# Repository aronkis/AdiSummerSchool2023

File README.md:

# AnalogDevices Summer School 2023

This is a repository for the Analog Devices summer school 2023.
We made a accelerometer application from designing the schematics to writing the code for the application.
We used a ADXL327 as an accelerometer and an AD5592R as the ADC.
Using KiCad we designed the schematics for this project as well as the layout.
The linux drivers were written in C, and the applications in C and in Python.

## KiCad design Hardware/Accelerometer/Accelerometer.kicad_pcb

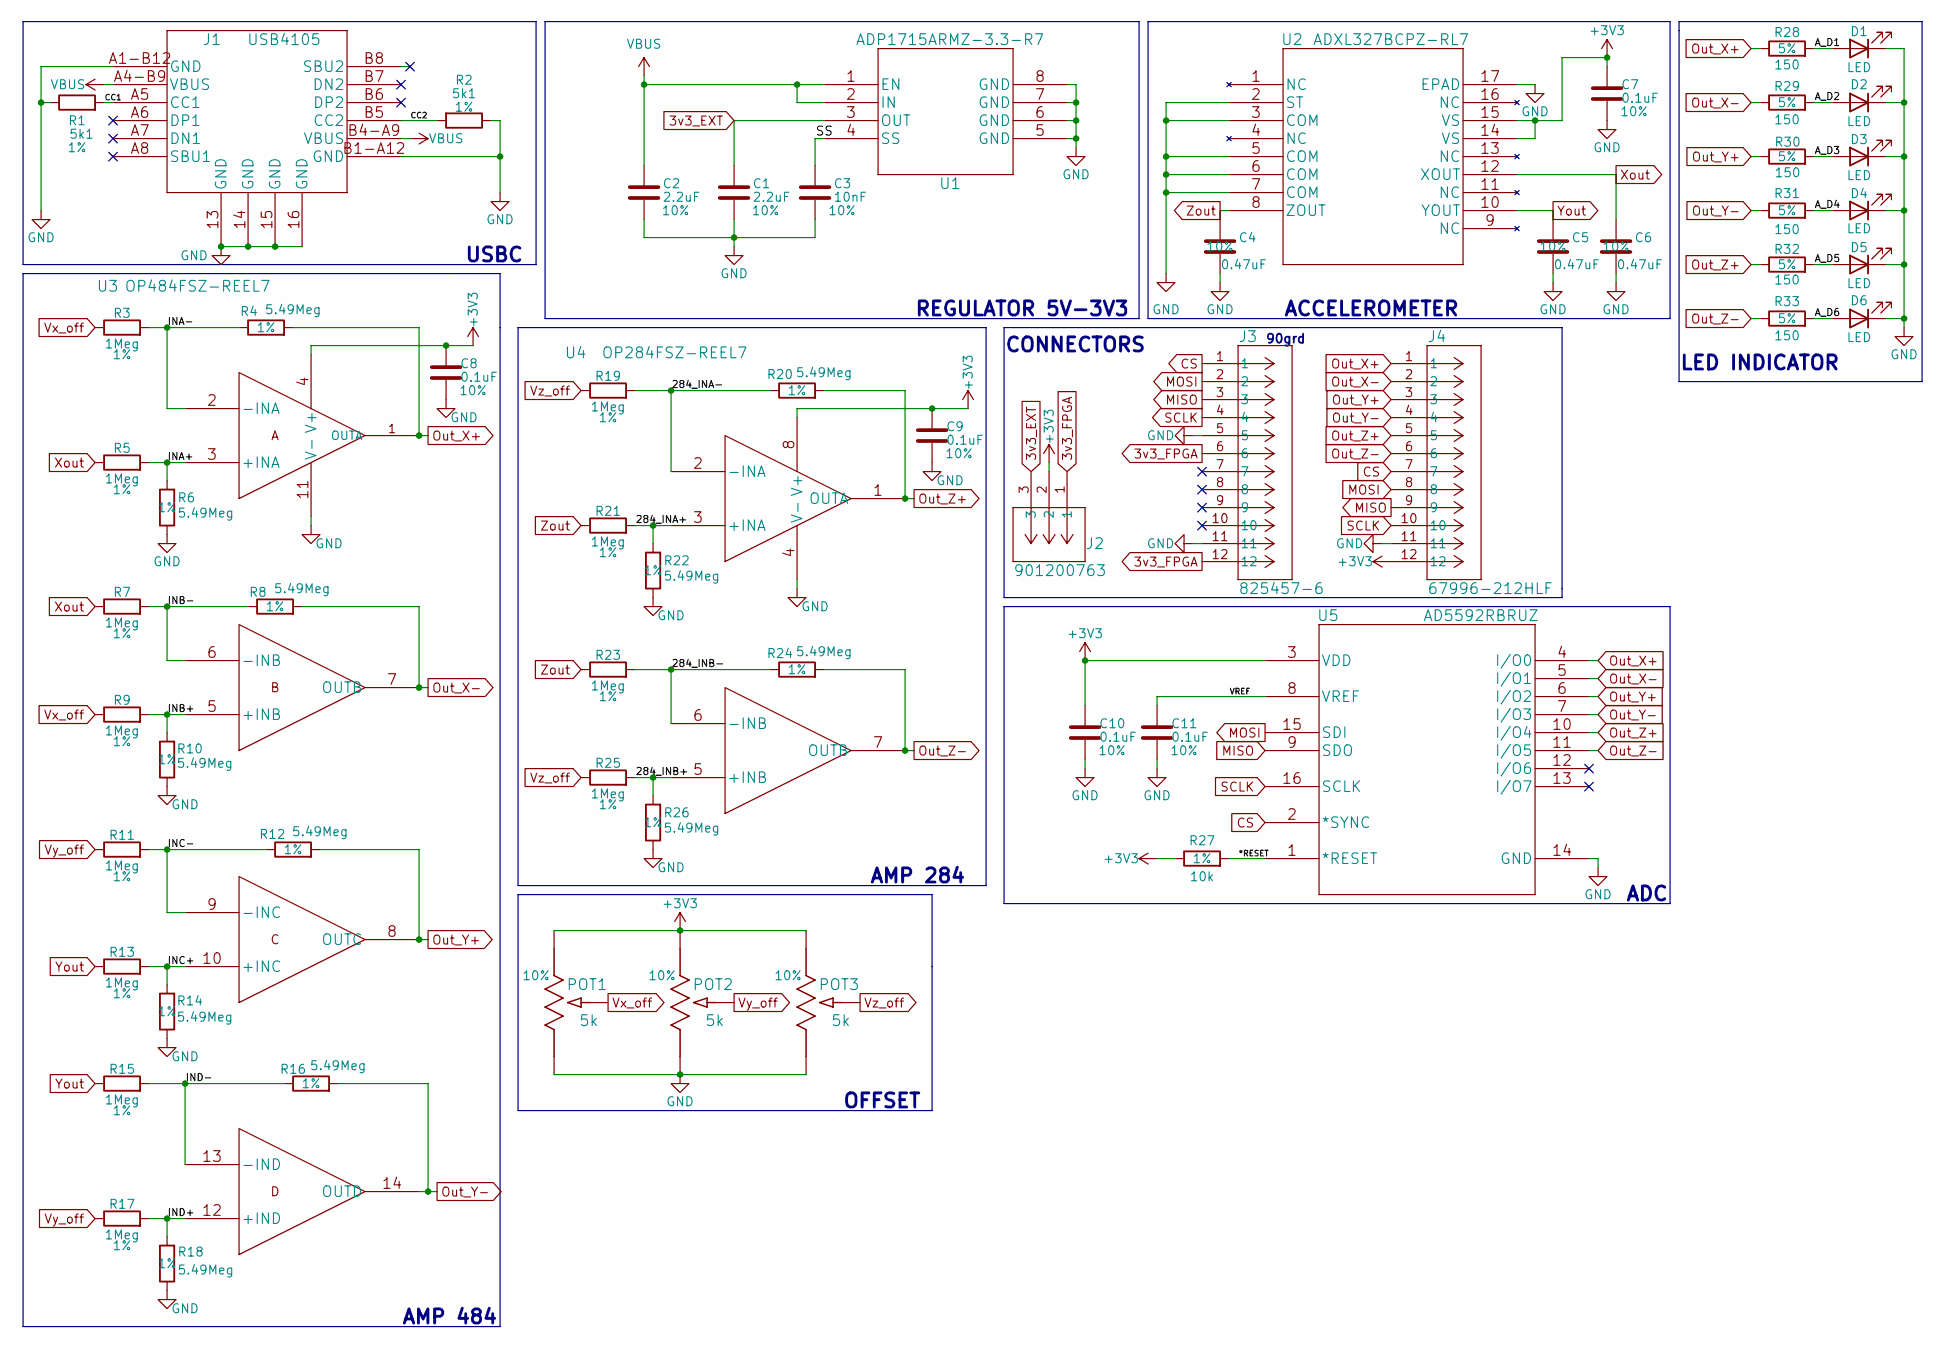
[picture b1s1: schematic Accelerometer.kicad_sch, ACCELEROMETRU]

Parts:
C1, C2: 2.2uF; C_0603_1608Metric; Tolerance 10%
C3: 10nF; C_0603_1608Metric; Tolerance 10%
C4: 0.47uF; C_0603_1608Metric; Tolernace 10%
C5, C6: 0.47uF; C_0603_1608Metric; Tolerance 10%
C7, C8, C9, C10, C11: 0.1uF; C_0603_1608Metric; Tolerance 10%
D1, D2, D3, D4, D5, D6: LED; D_0805_2012Metric
J1: USB4105; USB4105-GF-A
J2: 901200763; PinHeader_1x03_P2.54mm_Vertical
J3: 825457-6; CONN_2213S-30G_MTC_new
J4: 67996-212HLF; CONN_2213S-30G_MTC_new
POT1, POT2, POT3: 5k; POT_3386G; Tolerance 10%
R1, R2: 5k1; R_0603_1608Metric; Tolerance 1%
R3, R5, R7, R9, R11, R13, R15, R17, R19, R21, R23, R25: 1Meg; R_0603_1608Metric; Tolerance 1%
R4, R6, R8, R10, R12, R14, R16, R18, R20, R22, R24, R26: 5.49Meg; R_0603_1608Metric; Tolerance 1%
R27: 10k; R_0603_1608Metric; Tolerance 1%
R28, R29, R30, R31, R32, R33: 150; R_0603_1608Metric; Tolerance 5%
U1: ADP1715ARMZ-3.3-R7; RM_8_ADI
U2: ADXL327BCPZ-RL7; CP_16_5A_ADI
U3: OP484FSZ-REEL7; R_14_ADI
U4: OP284FSZ-REEL7; R_8_ADI
U5: AD5592RBRUZ; RU_16_ADI

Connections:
3v3_EXT: C1.1, J2.3, U1.3 (OUT)
3v3_FPGA: J2.1, J3.6, J3.12
+3V3: C7.1, C8.1, C9.1, C10.1, J2.2, J4.12, POT1.1, POT2.1, POT3.1, R27.1, U2.14 (VS), U2.15 (VS), U3.4 (V+), U4.8 (V+), U5.3 (VDD)
/284_INA+: R21.2, R22.2, U4.3 (+INA)
/284_INA-: R19.2, R20.1, U4.2 (-INA)
/284_INB+: R25.2, R26.2, U4.5 (+INB)
/284_INB-: R23.2, R24.1, U4.6 (-INB)
/*RESET: R27.2, U5.1 (*RESET)
/A_D1: D1.2 (A), R28.2
/A_D2: D2.2 (A), R29.2
/A_D3: D3.2 (A), R30.2
/A_D4: D4.2 (A), R31.2
/A_D5: D5.2 (A), R32.2
/A_D6: D6.2 (A), R33.2
/CC1: J1.A5 (CC1), R1.2
/CC2: J1.B5 (CC2), R2.2
/INA+: R5.2, R6.2, U3.3 (+INA)
/INA-: R3.2, R4.1, U3.2 (-INA)
/INB+: R9.2, R10.2, U3.5 (+INB)
/INB-: R7.2, R8.1, U3.6 (-INB)
/INC+: R13.2, R14.2, U3.10 (+INC)
/INC-: R11.2, R12.1, U3.9 (-INC)
/IND+: R17.2, R18.2, U3.12 (+IND)
/IND-: R15.2, R16.1, U3.13 (-IND)
/SS: C3.1, U1.4 (SS)
/VREF: C11.1, U5.8 (VREF)
CS: J3.1, J4.7, U5.2 (*SYNC)
GND: C1.2, C2.2, C3.2, C4.2, C5.2, C6.2, C7.2, C8.2, C9.2, C10.2, C11.2, D1.1 (K), D2.1 (K), D3.1 (K), D4.1 (K), D5.1 (K), D6.1 (K), J1.13 (GND), J1.14 (GND), J1.15 (GND), J1.16 (GND), J1.A1-B12 (GND), J1.B1-A12 (GND), J3.5, J3.11, J4.11, POT1.3, POT2.3, POT3.3, R1.1, R2.1, R6.1, R10.1, R14.1, R18.1, R22.1, R26.1, U1.5 (GND), U1.6 (GND), U1.7 (GND), U1.8 (GND), U2.2 (ST), U2.3 (COM), U2.5 (COM), U2.6 (COM), U2.7 (COM), U2.17 (EPAD), U3.11 (V-), U4.4 (V-), U5.14 (GND)
MISO: J3.3, J4.9, U5.9 (SDO)
MOSI: J3.2, J4.8, U5.15 (SDI)
Out_X+: J4.1, R4.2, R28.1, U3.1 (OUTA), U5.4 (I/O0)
Out_X-: J4.2, R8.2, R29.1, U3.7 (OUTB), U5.5 (I/O1)
Out_Y+: J4.3, R12.2, R30.1, U3.8 (OUTC), U5.6 (I/O2)
Out_Y-: J4.4, R16.2, R31.1, U3.14 (OUTD), U5.7 (I/O3)
Out_Z+: J4.5, R20.2, R32.1, U4.1 (OUTA), U5.10 (I/O4)
Out_Z-: J4.6, R24.2, R33.1, U4.7 (OUTB), U5.11 (I/O5)
SCLK: J3.4, J4.10, U5.16 (SCLK)
VBUS: C2.1, J1.A4-B9 (VBUS), J1.B4-A9 (VBUS), U1.1 (EN), U1.2 (IN)
Vx_off: POT1.2, R3.1, R9.1
Vy_off: POT2.2, R11.1, R17.1
Vz_off: POT3.2, R19.1, R25.1
Xout: C6.1, R5.1, R7.1, U2.12 (XOUT)
Yout: C5.1, R13.1, R15.1, U2.10 (YOUT)
Zout: C4.1, R21.1, R23.1, U2.8 (ZOUT)

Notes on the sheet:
ADC
90grd
LED INDICATOR
USBC
ACCELEROMETER
CONNECTORS
AMP 484
OFFSET
REGULATOR 5V-3V3
AMP 284

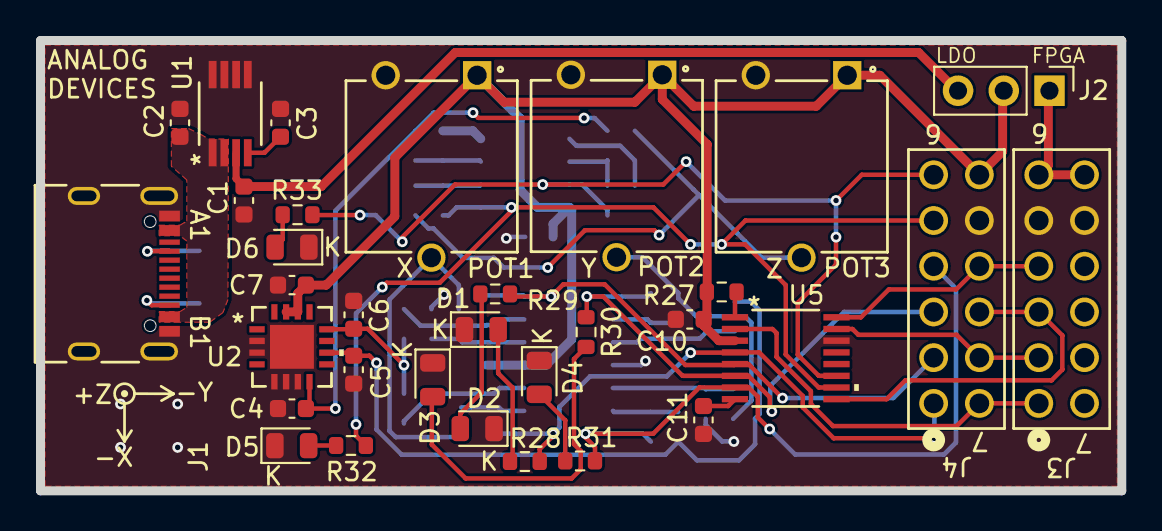
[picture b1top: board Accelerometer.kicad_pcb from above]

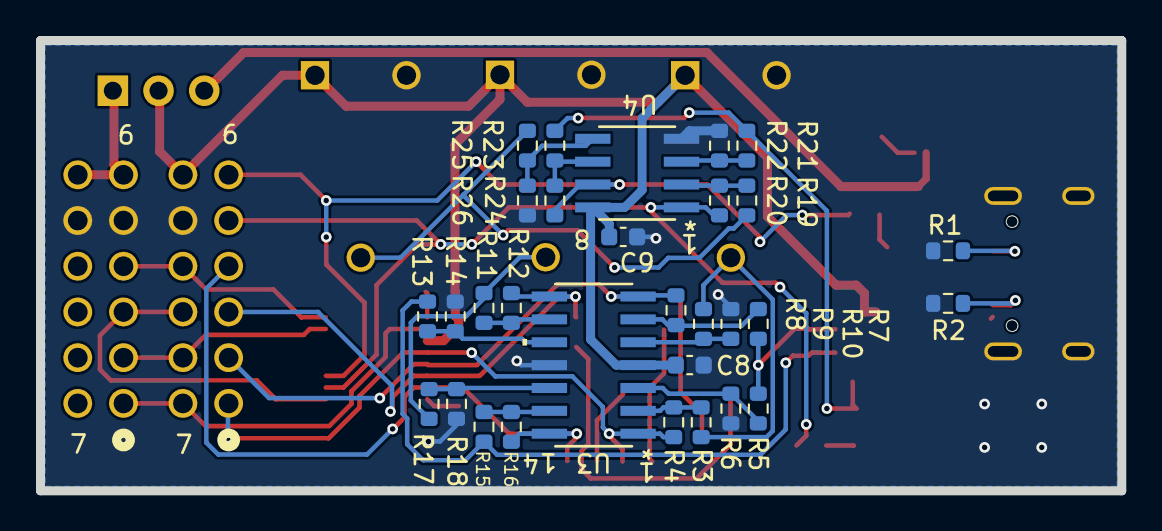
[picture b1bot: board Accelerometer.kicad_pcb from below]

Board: 2 copper layers, 60.1 x 25.0 mm, 62 parts (30 on the bottom side), 44 nets.

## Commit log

2023-08-25 Adding everything we have done at the ADISummerSchool2023.
2024-06-10 Readding the HDL folder without the .git folder.
